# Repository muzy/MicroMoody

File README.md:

# MicroMoody

RGB LED driven by an ATTiny85. Largely blink(1)-compatible, except that it uses
I2C instead of USB.

## setup

See <https://wiki.chaosdorf.de/MicroMoody> and
<https://wiki.raumzeitlabor.de/wiki/MicroMoody> for soldering instructions.

For the firmware, run `make && make program`. You may need to edit the
Makefile to fit your programmer, it's written for an usbasp.

## remote control (I2C)

This is enabled by the `-DI2CEN` compile flag, which is set by default in the
Makefile. Hardware pull-ups on SCL and SDA are required (1.5 kOhm recommended)

After sending the 7bit address and the r/!w bit,
the bus master must send the following 7 bytes to the MicroMoody:

* command
* delay
* red value
* green value
* blue value
* payload address (high byte)
* payload address (low byte)

The default I2C address is `0x11` (17),
The default payload address is `0x0001`. The idea behind this distinction is
to use the I2C address to talk to any micromoody, and the payload address to
select the specific micromoody to address. This way, you can have various
other I2C devices and up to 65534 MicroMoodies on the same bus
(just in case you need to).

Commands with the broadcast payload address of `0xffff` are always accepted,
even when they contain the "set address" opmode.

red, green and blue are the color value, 0 is off, 0xff is full brightness.

There are several types of commands:

### command 0 .. 127 (animation sequences)

*  0: Save `RGB` + delay in animation slot 1
* ...
* 111: Save `RGB` + delay in animation slot 112
* 112: run animation. It will start in slot 1 and end in the slot last set.
* 113: reserved
* ...
* 119: reserved

For instance, to set a steady red pulse, you can transmit (in hex)
`00 10 ff 00 00 ff ff`, `01 10 50 00 00 ff ff`. This will make the animation
run in slot 1 -> slot 2 -> slot 1 -> ....

Note that this does not start the animation yet, use `70 XX XX XX XX ff ff`
for that. Also note that the upper bound of the current sequence is
determined by the last animation command. So if you send `00 ...`,
`01 ...`, `02 ...`, `00 ...`, the animation run will be
slot 1 -> slot 1 -> slot 1 -> .... (i.e. a steady color).

Refer to example/\*/rgbpulse for a more sophisticated example.

### command 128 .. 239

reserved

### command 240 .. 255 (EEPROM)

These commands access the EEPROM. Writing one byte takes about 3.4ms and is
implemented synchronously, so expect them to be slow. They may even cause I2C
bus timeouts (which do not indicate write failures).

* 240: Save current mode of operation (last command &lt; 64) to EEPROM to be
       recalled after a power cycle. NOTE: if the current opmode is 63
       (animation), this may take up to 1 second (~12ms for each used animation
       slot)
* 241: Set address to color bytes. payload high = red, payload low = green,
       i2c = blue. This will also set the operation mode to random fading.
       Note that for i2c, the least significant 7 bit are the address, while
       the most significant bit is ignored.
       After setting the payload address, the moody will display it on the RGB
       LED.  The flash cycle is MSB ... LSB with a pause at the end, the i2c
       address is not displayed. cyan == 0, yellow == 1.

commands 242 to 255 are reserved for further EEPROM commands.

## I2C master hardware

If you have an Arduino, see `examples/arduino/SerialToI2C` for a USB-Serial
to I2C interface.

Otherwise, see [vusb-i2c](https://github.com/derf/vusb-i2c) for a
general-purpose USB-I2C tool based on VUSB.

## determining the firmware state

A newly flashed MicroMoody will pulse RGB colors (red -> off -> yellow -> off
-> ...).

After the address has been set, it will pulse yellow / cyan depending on the
payload address bits (see command 241).

## I2C master operation

NOT SUPPORTED RIGHT NOW.

When compiled with -DI2CMASTER (disabled by default), the MicroMoody will act
as I2C bus master. After each transition (after half the time until the next
transition has passed) it will send its current color and fade delay as a
broadcast (payload address 0xffff) over the bus. The I2C address used will be
the MicroMoody's I2C address (see above for default).

If it is operating with hard transitions, so will the slaves. same for soft
(fading) transitions.

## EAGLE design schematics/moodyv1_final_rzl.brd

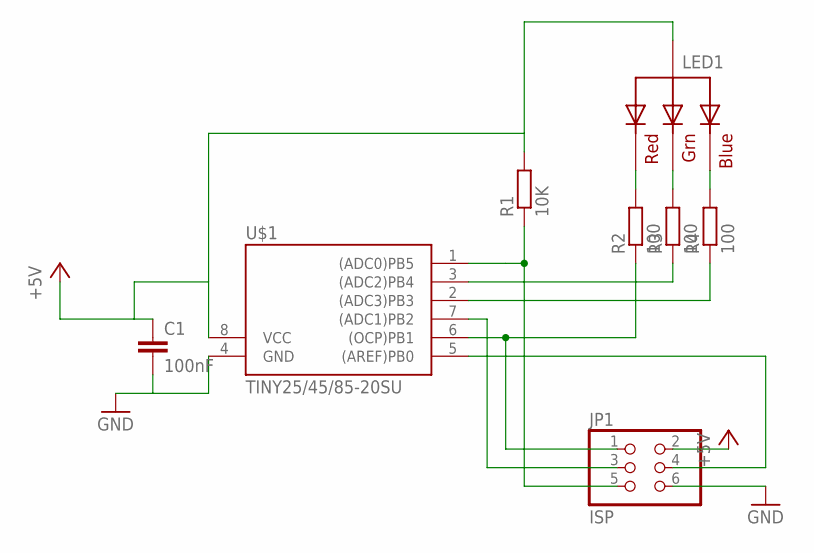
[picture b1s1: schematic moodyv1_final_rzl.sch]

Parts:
C1: 100nF; C0805
JP1: ISP; 2X03SMD
LED1: RGBLED_CA-PIRANHA; PIRANHA5MM
R1: 10K; R1206
R2, R3, R4: 100; R0805
U$1: TINY25/45/85-20SU; SOIC8

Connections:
+5V: C1.1, JP1.2, LED1.4 (VCC), R1.2, U$1.8 (VCC)
GND: C1.2, JP1.6, U$1.4 (GND)
unnamed: JP1.5, R1.1, U$1.1 ((ADC0)PB5)
unnamed: LED1.2 (RED), R2.2
unnamed: LED1.3 (GREEN), R3.2
unnamed: LED1.1 (BLUE), R4.2
unnamed: JP1.4, U$1.5 ((AREF)PB0)
unnamed: JP1.3, U$1.7 ((ADC1)PB2)
unnamed: JP1.1, R2.1, U$1.6 ((OCP)PB1)
unnamed: R4.1, U$1.2 ((ADC3)PB3)
unnamed: R3.1, U$1.3 ((ADC2)PB4)

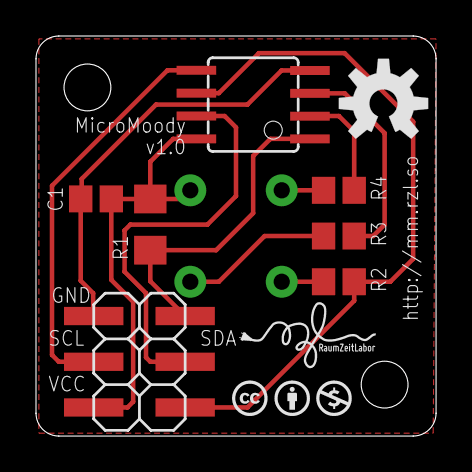
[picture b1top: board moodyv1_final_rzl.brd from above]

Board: 2 copper layers, 22.2 x 22.2 mm, 8 parts (1 on the bottom side), 11 nets.

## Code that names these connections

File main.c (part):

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#include <avr/interrupt.h>

/*
 * PB1: green (OC1A)
 * PB3: blue  (soft pwm)
 * PB4: red   (OC1B)
 */

#define VRED   ( OCR1B   )
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
#define TEMPERATURE_ZERO (355)

#define P_SDA PB0
#define P_SCL PB2

#ifdef I2CMASTER
#undef I2CEN
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{
	
	DDRB = _BV(DDB1) | _BV(DDB3) | _BV(DDB4);
	PORTB = _BV(PB1) | _BV(PB3) | _BV(PB4);

	uint8_t cnt = 0;

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	while (1) {
		cnt++;
		if (cnt == 0 && VBLUE) {
			PORTB &= ~_BV(PB3);
		}
		if (cnt == VBLUE)
			PORTB |= _BV(PB3);
	}

	return 0;
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 */

void sda_high() {
	DDRB  &= ~_BV(PB0);
}

void sda_low() {
	DDRB  |=  _BV(PB0);
}

void scl_high() {
	DDRB  &= ~_BV(PB2);
}

void scl_low() {
	DDRB  |=  _BV(PB2);
}

void twi_delay(uint8_t delay)
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
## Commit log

2013-03-15 Add schematic
2013-03-15 add makefile template
2013-03-15 move schematics to folder schematics
2013-03-15 work work work
2013-03-15 update gitignore
2013-03-15 fading demo code using soft pwm
2013-04-19 use hardware pwm for green and red
2013-04-25 main.c: Allow faster fading
2013-04-25 shorten makefile
2013-04-25 implement various blinkenlight modes (based on blinkencontrol). TODO: I2C
2013-05-10 working I2C communication \o/
2013-05-12 store and recall opmode in EEPROM
2013-05-12 documentation / README
2013-05-12 implement fade on/off and blink on/off
2013-05-12 makefile: add .lss target (assembly listing)
2013-05-12 split up mode and speed into separate bytes
2013-05-12 change default address to 0x0000 (0x0001 is borked)
2013-05-12 tried to fix addrlo receive. still unreliable. what!
2013-05-13 fix fading (allow time for full 0xff <-> 0x00 transition)
2013-05-13 re-order modes
2013-05-13 Now: Real I2C. with start condition detection and no bugs so far
2013-05-13 add I2C command to set address
2013-05-13 README: Add link to USB -> I2C bridge
2013-05-13 add newest schematic
2013-05-13 remove uneccesary files
2013-05-17 enable temperature mode. it's still broken.
2013-05-17 RGB fading: stay a while at a color before fading to next
2013-05-19 add parts image (to be used in manual)
2013-05-20 add circuit.png
2013-05-20 add broadcast address
2013-05-20 Fix ADC initialization (temperature sensor readout should work now)
2013-05-26 add (not very good) I2C bus master support
2013-05-28 run I2C master code without flickering
2013-05-29 i2cmaster: wait less than 50% until command propagation
2013-05-31 fix variable mis-declaration without I2CMASTER
2013-06-04 main.c: add ISC license
2013-06-07 leave space for I2C ack bit (we don't send an ack yet, though!)
2013-07-12 proper i2c support with ack (and nak after last byte)
2013-07-25 fix off-by-one in addr_i2c (write == 0, we don't support read...)
2013-07-26 fix i2c address usage
2013-07-28 fix i2c master mode
2013-07-29 read out temperature via I2C. Not tested with multiple moodies on a bus yet
2013-07-31 add example code for an Arduino as I2C bus master
2013-07-31 Revert "add example code for an Arduino as I2C bus master" (wrong branch)
    This reverts commit cb93c6431dd53ad0109b894a79997bde237eed0c.
2013-07-31 Add example for an arduino as i2c master and three modies
2013-07-31 do not save opmode by default, send 0x20 to do so
2013-07-31 Arduino/Wire example: shorten code
2013-07-31 add vusb-i2c example
2013-08-03 second byte is delay, not speed
2013-08-03 change "save state" and "set address" commands to 0xf0 / 0xf1
2013-08-03 Add support for custom animations (up to 64 steps). blink(1)-like.
2013-08-03 add rgbpulse example (demonstrating the new animation support)
2013-08-03 add RGBPulse arduino example (identical to vusb-i2c/rgbpulse)
2013-08-03 do not add wait-states while fading (shiny pulsing)
2013-08-03 adjust rgbpulse example for new firmware behaviour
2013-08-03 Add arduino serial -> I2C example
2013-08-03 README: Update remote control
2013-08-04 rework readme
2013-09-07 3rgbfade: slightly slower transitions
2013-09-07 initial stepfade support, no preset animations for now
2013-09-07 fix is_b(lue) renaming mistake
2013-09-07 add default eeprom
2013-09-09 blink own address after setting it
2013-09-09 throw out preset animations for now. Enlarge animation memory.
2013-09-09 use __flash feature instead of pgmspace.h
2013-09-09 do not fade if delay==0
2013-09-09 speed -> delay
2013-09-10 immediate transition if slot == delay == 0
2013-09-10 update rgbpulse example
2013-09-10 example/arduino: adjust mode and delay
2013-09-10 fix wrong eeprom usage
2013-09-10 RGB3fade example: adjust sleep times
2014-06-21 3rgbfade example: get parameters from commandline args
2015-08-01 add 3rgbpulse example
2016-01-17 USI receive: Fix a (surprisingly harmess) typo after receipt of the last byte
2016-01-17 Makefile: improve avr-size output
2016-01-17 I2C receive: Acknowledge the last byte

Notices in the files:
main.c:
Copyright (c) 2013, Daniel Friesel <derf@chaosdorf.de>
